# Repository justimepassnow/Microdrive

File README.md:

# μDrive (Microdrive)

**μDrive** is an open-source hardware and software project designed to convert any standard "dumb" DC motor into a smart, closed-loop servo motor. By retrofitting a standard DC motor with an analog potentiometer or an I2C magnetic encoder, μDrive grants you precise control over position, velocity, and current.

---

## ✨ Features

* **Universal DC Motor Support:** Works with standard DC brushed motors (within the limits of the onboard motor driver).
* **Closed-Loop Control:** PID-based control over Motor Position, Velocity, and Torque.
* **Single-Wire Communication:** Network multiple servos together using a half-duplex, single-wire UART interface.
* **Web-Based Dashboard:** Includes a Svelte-based WebGUI utilizing the Web Serial API. Connect a master microcontroller to your PC via USB, and monitor/tune your servo network directly from your browser.
* **High-Level API:** Control motors using high-level commands without worrying about register-level or bit-level operations.

---

## 📖 Documentation

A comprehensive documentation suite is available in the [docs](docs/) directory:
* **[Hardware Reference](docs/hardware.md):** Detailed specs of both board variants, pin mappings, and BOM.
* **[Firmware Guide](docs/firmware.md):** Protocol specifications, PID loop details, and compilation/flashing guide.
* **[Getting Started](docs/getting-started.md):** Step-by-step instructions from zero to a running servo network.
* **[MicroPython API Reference](docs/api-reference.md):** Comprehensive reference for the library, utility scripts, and wiring.

---

## 🛠️ Hardware Specifications

μDrive is available in **two PCB variants** sharing the same MCU and logic, but using different motor drivers:

| Feature | Servo Board | MG996 Drop-in Board |
|---|---|---|
| **Motor Driver** | CP2119 | BDR6121H |
| **Form Factor** | Standard — attach to any DC motor | Drop-in replacement for MG996R servo |
| **Operating Voltage** | Up to 18V max | Up to 7.5V max |
| **Current Rating** | 5A continuous | 1.5A continuous / 3A peak |
| **PCB Files** | [servo_pcb](PCB/) | [servo_pcb_mg99x](PCB/) |

### Board Layouts

### Common Architecture (Both Boards)
* **Microcontroller:** MindMotion MM32G0001 (32-bit Cortex-M0, 48MHz, 16KB Flash, 2KB RAM)
* **Current Sensor:** INA180A2 (current sense amplifier) with a 0.01Ω shunt resistor for overcurrent protection
* **Power:** Onboard SL7533-3 3.3V logic regulator (supports input up to 24V)
* **Feedback Inputs:**
  * **Analog:** Standard potentiometer support (shared with the SDA pin).
  * **Digital (I2C):** 4-pad footprint (3.3V, SCL, SDA, GND) for external I2C magnetic encoders like the AS5600.
* **Communication:** Half-duplex, single-wire UART on PA12 (open-drain), 250000 baud, 8N1.

---

## 💻 Software & APIs

The project uses a Master/Slave architecture over a half-duplex UART bus. You simply import the driver library onto your master microcontroller and send high-level commands.

* **MicroPython:** A fully functioning driver library is currently available.
* **Arduino/C++:** *Coming soon!*

### WebGUI Architecture

```mermaid
graph TD
    Web["<span style='color:#000'>💻 Web Browser<br>(Svelte WebGUI)</span>"] -- "Web Serial API" --> Master["<span style='color:#000'>🧠 Master Microcontroller<br>(Running Python Script)</span>"]
    Master -- "Single-Wire UART" --> Servo["<span style='color:#000'>⚡ μDrive Servo Board</span>"]
    Servo --> Motor["<span style='color:#000'>⚙️ DC Motor + Encoder</span>"]

    %% Styling
    style Web fill:#e1f5fe,stroke:#01579b,stroke-width:2px;
    style Master fill:#e8f5e9,stroke:#1b5e20,stroke-width:2px;
    style Servo fill:#fff3e0,stroke:#e65100,stroke-width:2px;
    style Motor fill:#efebe9,stroke:#3e2723,stroke-width:2px;
```

<br>

### Web GUI

<br>

---

## 🚀 Getting Started

### 1. Flashing the Servo Board (via Picoprobe)

> *Why use a Raspberry Pi Pico?*
> Programming obscure chips like the MM32G0001 usually requires buying dedicated, expensive hardware programmers (like mm32link or ST-Link). By using a $4 Raspberry Pi Pico instead, we keep the project incredibly cheap and accessible. Even better: once you've flashed the servo board, you can wipe the Pico and reuse it as the master MicroPython controller for your entire servo network!

**Step 1: Turn the Pico into a Programmer**
Flash your Raspberry Pi Pico with the **Picoprobe** (Debug Probe) firmware to turn it into a CMSIS-DAP debugger. You can download the latest `debugprobe_on_pico.uf2` file directly from the [official Raspberry Pi GitHub Releases page](https://github.com/raspberrypi/debugprobe/releases). Just hold the BOOTSEL button, plug in the Pico, and drag-and-drop the file!

**Step 2: Wire the Pico to the μDrive Board**
Connect these 4 wires from the Pico to the programming header on the μDrive board:
* **Pico 3V3**  -->  **μDrive 3.3V**
* **Pico GND**  -->  **μDrive GND**
* **Pico GP2**  -->  **μDrive SWCLK** (Labeled **C** on the board)
* **Pico GP3**  -->  **μDrive SWDIO** (Labeled **D** on the board)

**Step 3: Install the Software Tools**
1. Install **VS Code** and add the **PlatformIO** extension.
2. Install **Python** on your PC.
3. Open a terminal and install the flashing tool by running: `pip install pyocd`
   * *(**Windows Users:** If `pyocd` fails to detect your probe later, Windows likely installed the wrong default driver. Download the free [Zadig tool](https://zadig.akeo.ie/), select "Picoprobe CMSIS-DAP" from the dropdown, and replace the driver with **WinUSB**).*

**Step 4: Open and Flash!**
1. Clone this repository and open the `Microdrive` folder in VS Code.
2. Click the PlatformIO **Upload** button (the small `→` arrow at the bottom of the screen). PlatformIO will automatically compile the code and trigger `pyocd` to flash it onto the MM32G0001!

### 2. Setting Up the Master MCU (Drivers)
Once the servo board is flashed, it listens for commands over a half-duplex UART line. You will need a "Master" microcontroller to send these commands.
* Currently, a **MicroPython** driver is provided. You can flash a standard Raspberry Pi Pico with MicroPython, import the provided driver library, and use simple high-level functions to command the servo.
* *(Arduino/C++ library support is coming soon!)*

### 3. Launching the Web GUI
To easily tune and monitor your servo network from your computer, you can run the provided Svelte WebGUI:
1. Ensure your Master MCU is connected to your PC via USB and running the serial bridge python script.
2. Open a terminal and navigate to the `gui` folder inside this repository.
3. Run `npm install` to download the web dependencies.
4. Run `npm run dev` to start the local server.
5. Open the provided `localhost` link in a browser that supports the Web Serial API (like Chrome or Edge) to connect to your Master MCU and start tuning!

---

## 🚧 Known Issues & Roadmap

Microdrive is actively under development. Current focus areas include:

* **🐛 EMI Stability:** The board occasionally stops responding to commands during massive current spikes. This is likely due to electromagnetic interference (EMI) crashing the MCU or bus. Hardware/software filtering improvements are being investigated.
* **🚀 Better I2C Encoder Support:** Writing the software drivers to fully utilize the AS5600 footprint.
* **⚙️ Control Optimization:** Improving the efficiency of the communication protocol and fine-tuning the torque and velocity control loops.
* **🔌 Arduino Compatibility:** Development of Arduino/C++ compatible driver libraries to control the servo network from Arduino-compatible microcontrollers.

---

## 🤝 Contributing

Contributions are welcome! Whether it's firmware, hardware, documentation, or the WebGUI — check out the [Contributing Guide](CONTRIBUTING.md) to get started. Found a bug or have an idea? [Open an issue](https://github.com/justimepassnow/Microdrive/issues).

---

## ⚖️ License

This project is fully open-source and [OSHWA certified](https://certification.oshwa.org/in000092.html) (**UID: IN000092**):
* The **Software/Firmware** is licensed under the [MIT License](LICENSE).
* The **Hardware (PCBs/Schematics)** is licensed under the [CERN-OHL-P v2](LICENSE-HARDWARE.txt).

You are free to build, modify, and integrate μDrive into your own projects (commercial or hobbyist).

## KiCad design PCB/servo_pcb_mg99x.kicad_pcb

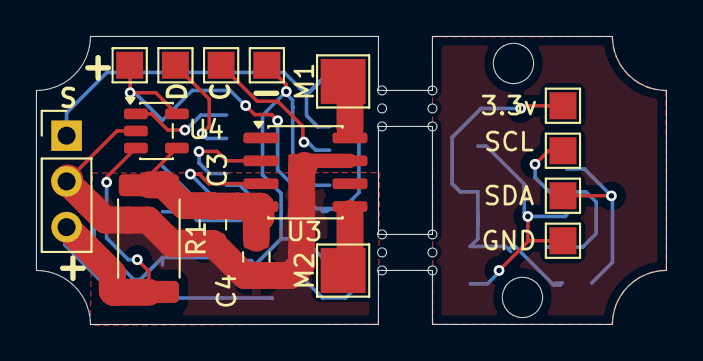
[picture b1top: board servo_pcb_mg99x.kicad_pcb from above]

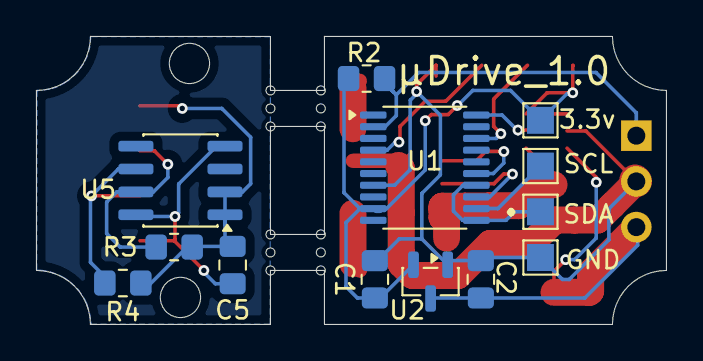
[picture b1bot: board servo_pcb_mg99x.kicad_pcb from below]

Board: 2 copper layers, 35.0 x 16.0 mm, 29 parts (13 on the bottom side), 18 nets.

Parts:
C1, C4: 10uf; C_0805_2012Metric_Pad1.18x1.45mm_HandSolder
C2, C3, C5: 100nf; C_0805_2012Metric_Pad1.18x1.45mm_HandSolder
J1: power in; PinHeader_1x03_P2.54mm_Vertical
M1: M1; TestPoint_Pad_2.5x2.5mm
M2: M2; TestPoint_Pad_2.5x2.5mm
R1: 0.01R; R_2512_6332Metric
R2, R3, R4: 10K; R_0805_2012Metric_Pad1.20x1.40mm_HandSolder
TP1, TP7: 3.3v; TestPoint_Pad_1.5x1.5mm
TP2, TP10: GND; TestPoint_Pad_1.5x1.5mm
TP3: SWCLK; TestPoint_Pad_1.5x1.5mm
TP4: -VE; TestPoint_Pad_1.5x1.5mm
TP5: +VE; TestPoint_Pad_1.5x1.5mm
TP6: SWIO; TestPoint_Pad_1.5x1.5mm
TP8, TP11: SDA; TestPoint_Pad_1.5x1.5mm
TP9, TP12: SCL; TestPoint_Pad_1.5x1.5mm
U1: MM32G0001; TSSOP-20_4.4x6.5mm_P0.65mm
U2: SL7533-3; SOT-23
U3: BDR6121H; SOIC-8_3.9x4.9mm_P1.27mm
U4: INA180A2; SOT-23-5
U5: AS5600; SOIC-8_3.9x4.9mm_P1.27mm

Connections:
+3.3V: C1.1, R2.1, TP5.1, TP7.1, U1.9 (VDD), U2.2 (VOUT), U4.5 (V+)
/Angle: TP8.1, U1.11 (PA4), U1.14 (PA7)
/Current Read: U1.20 (PA2), U4.1
/DATA: J1.1, R2.2, U1.2 (PA12)
/DRIVER VCC: C3.1, C4.1, R1.1, U3.4 (VDD), U4.4 (-)
/INA: U1.13 (PA6), U3.3 (INB)
/INB: U1.15 (PA8), U3.2 (INA)
/SCL: TP9.1, U1.12 (PA5)
GND: C1.2, C2.2, C3.2, C4.2, J1.2, TP4.1, TP10.1, U1.7 (VSS), U2.1 (GND), U3.7 (GND), U4.2 (GND)
unnamed: TP6.1, U1.18 (PA13/SWDIO)
unnamed: TP3.1, U1.4 (PA14/SWCLK/NRST)
unnamed: M1.1, U3.8 (OUTA)
unnamed: M2.1, U3.5 (OUTB)
unnamed: C5.2, TP2.1, U5.4 (GND), U5.8 (DIR)
unnamed: R3.2, TP12.1, U5.7 (SCL)
unnamed: R4.2, TP11.1, U5.6 (SDA)
unnamed: C5.1, R3.1, R4.1, TP1.1, U5.1 (VDD5V), U5.2 (VDD3V3)
VCC: C2.1, J1.3, R1.2, U2.3 (VIN), U4.3 (+)

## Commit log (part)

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2026-06-07 Initial commmit for MicroDrive
2026-06-07 Readme updated
2026-06-07 Cleaned up PCB folder and updated readme, updated pcb
2026-06-08 cleaned up older pcbs and updated the master pcb
2026-06-08 updated pcb:added ground pours
2026-06-08 added licensing details
2026-06-08 updatedd license
2026-06-10 updated the pcb for generic motors
2026-06-11 updated docs
2026-06-12 fix: add hardware watchdog (IWDG) and disable debug UART from ISR context
    - Enable IWDG with ~500ms timeout for automatic MCU recovery when
    main loop hangs (no manual reset or power cycle needed)
    - Set DEBUG_LOG=0 to eliminate SysTick/UART race condition where
    print_status() from pid_update() could preempt send_status_reply()
    mid-transmission, permanently deadlocking the UART in RX mode
    - Add PA11 reset button footprint to PCB
2026-06-13 docs: added OSHWA certification, contributing guide, and issue templates
2026-06-19 feat: refactor current sampling to interrupts and build a GUI calibration wizard & step tester
    Firmware:
    - Replaced CPU-blocking polling loop in current sampling with an interrupt-driven mechanism to capture motor phase current at the PWM midpoint.
    - Added IRQ disabling/restoring in `adc_read()` to prevent race conditions and state corruption during concurrent ADC reads.
    - Extracted direct timer PWM compare writes into a helper `motor_set_pwm_pair` for cleaner register management.
    - Commented out IWDG watchdog configuration due to improper initialization
    - Configured SysTick NVIC priority to 0 (highest).
2026-06-19 docs: align documentation and comments with implementation specifications
    - Correct Servo ID range to 0-127 (due to 7-bit packing with direction bit) in docs and main.c comment
    - Update ServoConfig struct size documentation to 30 bytes (accounting for the 4-byte magic word)
    - Document the soft current limiting (admittance yield loop) algorithm and ISR priorities in docs/firmware.md
    - Update is_holding API description to reflect admittance yield compliance mode
    - Add the missing dir_pin constructor parameter to the ServoBus class documentation
    - Fix the MG99x schematic filename in docs/hardware.md
2026-06-19 refactor: simplify current sampling, tune serial priority, and fix slider bindings
    - Remove complex midpoint-synchronized current sampling logic and TIM1 interrupts from src/main.c.
    - Perform direct synchronous ADC current reads with calibrated offset and scaling (slope = 1.480 mA/count).
    - Increase USART1 IRQ priority and implement a 5ms inter-byte timeout to reset the packet parser state.
    - Reduce discovery scan range from IDs 0-253 to 0-127 in micropython/serial_proxy.py and gui/src/App.svelte.
    - Replace double-binding in gui/src/components/ControlDial.svelte with explicit oninput assignment handlers.
    - Increase the MicroPython reply timeout from 5ms to 8ms in micr
2026-06-25 docs: reorganize PCB images, rename generic board variant, and modernize diagrams
    - Relocate and rename PCB images (`servo_pcb_front.jpg` and `servo_pcb_back.jpg`) to `docs/images/`.
    - Embed PCB layouts and the Web GUI screenshot (`webgui.jpg`) in `README.md` with appropriate spacing and headings.
    - Rename references of "Generic Servo Board" to "Servo Board" and "Generic" form factor to "Standard" in `README.md`, `docs/hardware.md`, `docs/getting-started.md`, and
    issue templates for consistency.
    - Replace all legacy ASCII art drawings in the `docs/` folder with styled, modern Mermaid.js diagrams.
    - Optimize Mermaid layouts (text contrast in dark mode, vertical pin stack
2026-06-30 fix:update pcb footprint error ,cleanup micropython code

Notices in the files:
README.md:
License: MIT
Hardware License
